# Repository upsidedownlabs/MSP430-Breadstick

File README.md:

# MSP430 Breadstick

Upside Down Labs MSP430 Breadstick is a development board for ultra low power MSP430G2553 MCU from Texas Instruments. 

## Variant: Cheese Dip
Cheese Dip variant of MSP430 Breadstick comes with CH340C USB to UART bridge.

| Front              |  Back |
| :-------------------------: | :-------------------------: |
|   |  |

|Pinout|
| :--: |
||

| Dimensions              |  Schematic |
| :-------------------------: | :-------------------------: |
| 60.00 x 21.60 mm  |  |

## Variant: Apple Sauce
Apple Sauce variant of MSP430 Breadstick comes with FT232RQ USB to UART bridge.

| Front              |  Back |
| :-------------------------: | :-------------------------: |
|   |  |

| Dimensions              |  Schematic |
| :-------------------------: | :-------------------------: |
| 65.786 x 18.542 mm  |  |

## License

#### Hardware
CERN Open Hardware License Version 2 - Strongly Reciprocal ([CERN-OHL-S-2.0](https://spdx.org/licenses/CERN-OHL-S-2.0.html)).

#### Software
MIT open source [license](http://opensource.org/licenses/MIT).

#### Documentation:
<br />This work is licensed under a <a rel="license" href="http://creativecommons.org/licenses/by/4.0/">Creative Commons Attribution 4.0 International License</a>.

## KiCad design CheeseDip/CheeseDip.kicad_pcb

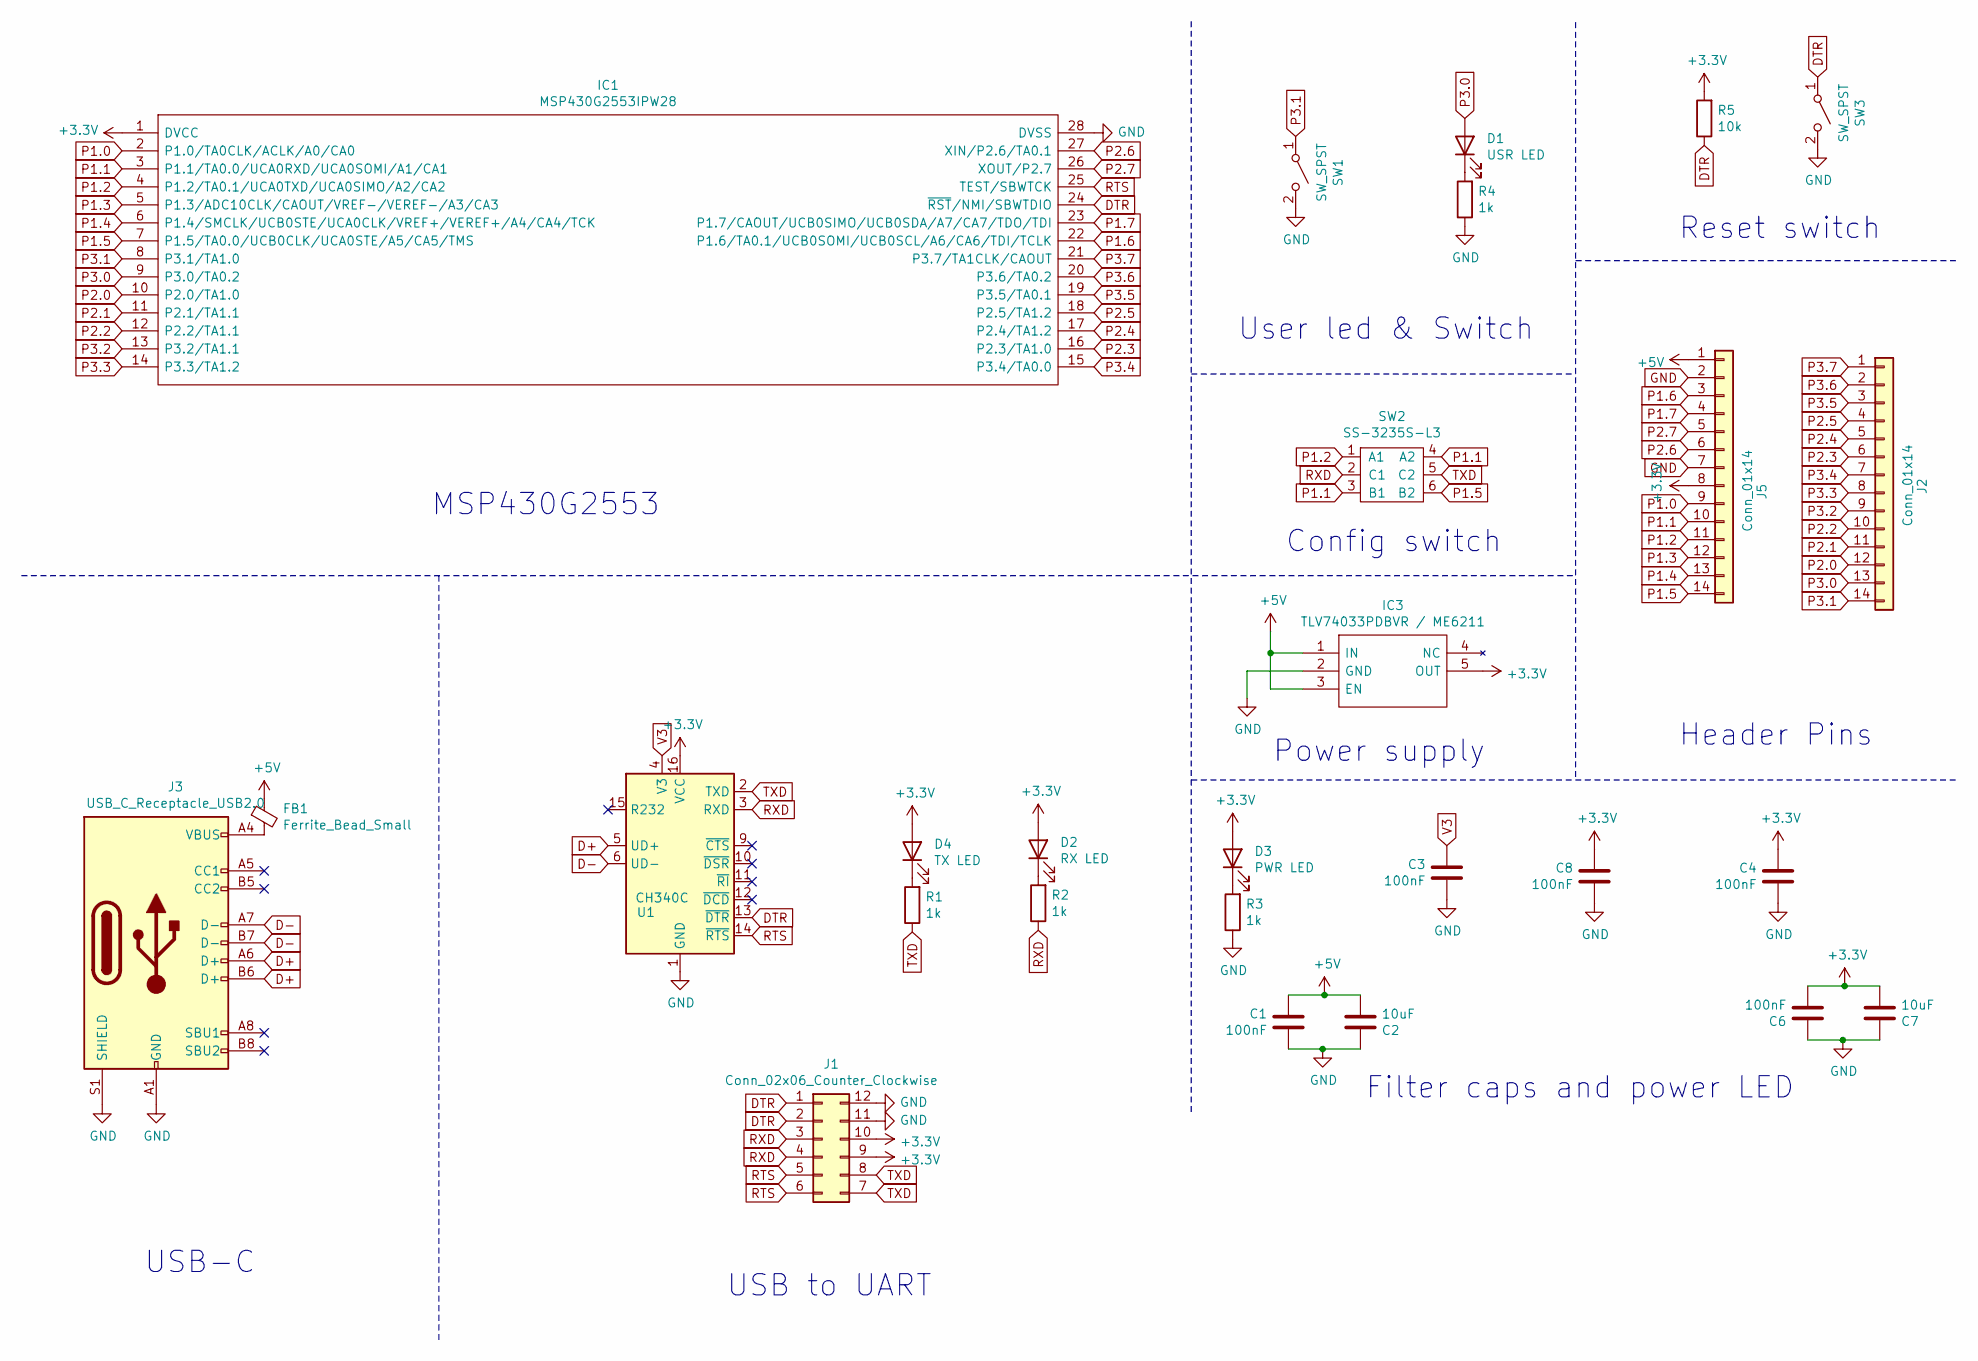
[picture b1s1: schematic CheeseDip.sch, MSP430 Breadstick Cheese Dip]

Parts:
C1, C3, C4, C6, C8: 100nF; C_0603_1608Metric_Pad1.08x0.95mm_HandSolder
C2, C7: 10uF; C_0805_2012Metric_Pad1.18x1.45mm_HandSolder
D1: USR LED; LED_0603_1608Metric_Pad1.05x0.95mm_HandSolder
D2: RX LED; LED_0603_1608Metric_Pad1.05x0.95mm_HandSolder
D3: PWR LED; LED_0603_1608Metric_Pad1.05x0.95mm_HandSolder
D4: TX LED; LED_0603_1608Metric_Pad1.05x0.95mm_HandSolder
FB1: Ferrite_Bead_Small; L_0805_2012Metric_Pad1.15x1.40mm_HandSolder
IC1: MSP430G2553IPW28; Manufacturer_Part_Number MSP430G2553IPW28; Mouser Part Number 595-MSP430G2553IPW28
IC3: TLV74033PDBVR / ME6211; TLV74033PDBVR; Manufacturer_Part_Number TLV74033PDBVR
J1: Conn_02x06_Counter_Clockwise; progMSP
J2, J5: Conn_01x14; PinHeader_1x14_P2.54mm_Vertical
J3: USB_C_Receptacle_USB2.0; USB_C_Receptacle_HRO_TYPE-C-31-M-12
R1, R2, R3, R4: 1k; R_0603_1608Metric_Pad0.98x0.95mm_HandSolder
R5: 10k; R_0603_1608Metric_Pad0.98x0.95mm_HandSolder
SW1, SW3: SW_SPST; SW_SPST_SKQG_WithStem
SW2: SS-3235S-L3
U1: CH340C; SOIC-16_3.9x9.9mm_P1.27mm

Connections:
+3V3: C4.1, C6.2, C7.2, C8.1, D2.2 (A), D3.2 (A), D4.2 (A), IC1.1 (DVCC), IC3.5 (OUT), J1.9, J1.10, J5.8, R5.2, U1.16 (VCC)
+5V: C1.1, C2.2, FB1.1, IC3.1 (IN), IC3.3 (EN), J5.1
D+: J3.A6 (D+), J3.B6 (D+), U1.5 (UD+)
D-: J3.A7 (D-), J3.B7 (D-), U1.6 (UD-)
DTR: IC1.24 (~RST~/NMI/SBWTDIO), J1.1, J1.2, R5.1, SW3.1 (A), U1.13 (~DTR)
GND: C1.2, C2.1, C3.2, C4.2, C6.1, C7.1, C8.2, IC1.28 (DVSS), IC3.2 (GND), J1.11, J1.12, J3.A1 (GND), J3.A12 (GND), J3.B1 (GND), J3.B12 (GND), J3.S1 (SHIELD), J5.2, J5.7, R3.1, R4.1, SW1.2 (B), SW3.2 (B), U1.1 (GND)
unnamed: D1.1 (K), R4.2
unnamed: D2.1 (K), R2.2
unnamed: D3.1 (K), R3.2
unnamed: D4.1 (K), R1.2
unnamed: FB1.2, J3.A4 (VBUS), J3.A9 (VBUS), J3.B4 (VBUS), J3.B9 (VBUS)
P1.0: IC1.2 (P1.0/TA0CLK/ACLK/A0/CA0), J5.9
P1.1: IC1.3 (P1.1/TA0.0/UCA0RXD/UCA0SOMI/A1/CA1), J5.10, SW2.3 (B1), SW2.4 (A2)
P1.2: IC1.4 (P1.2/TA0.1/UCA0TXD/UCA0SIMO/A2/CA2), J5.11, SW2.1 (A1)
P1.3: IC1.5 (P1.3/ADC10CLK/CAOUT/VREF-/VEREF-/A3/CA3), J5.12
P1.4: IC1.6 (P1.4/SMCLK/UCB0STE/UCA0CLK/VREF+/VEREF+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), J5.13
P1.5: IC1.7 (P1.5/TA0.0/UCB0CLK/UCA0STE/A5/CA5/TMS), J5.14, SW2.6 (B2)
P1.6: IC1.22 (P1.6/TA0.1/UCB0SOMI/UCB0SCL/A6/CA6/TDI/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), J5.3
P1.7: IC1.23 (P1.7/CAOUT/UCB0SIMO/UCB0SDA/A7/CA7/TDO/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), J5.4
P2.0: IC1.10 (P2.0/TA1.0), J2.12
P2.1: IC1.11 (P2.1/TA1.1), J2.11
P2.2: IC1.12 (P2.2/TA1.1), J2.10
P2.3: IC1.16 (P2.3/TA1.0), J2.6
P2.4: IC1.17 (P2.4/TA1.2), J2.5
P2.5: IC1.18 (P2.5/TA1.2), J2.4
P2.6: IC1.27 (XIN/P2.6/TA0.1), J5.6
P2.7: IC1.26 (XOUT/P2.7), J5.5
P3.0: D1.2 (A), IC1.9 (P3.0/TA0.2), J2.13
P3.1: IC1.8 (P3.1/TA1.0), J2.14, SW1.1 (A)
P3.2: IC1.13 (P3.2/TA1.1), J2.9
P3.3: IC1.14 (P3.3/TA1.2), J2.8
P3.4: IC1.15 (P3.4/TA0.0), J2.7
P3.5: IC1.19 (P3.5/TA0.1), J2.3
P3.6: IC1.20 (P3.6/TA0.2), J2.2
P3.7: IC1.21 (P3.7/TA1CLK/CAOUT), J2.1
RTS: IC1.25 (TEST/SBWTCK), J1.5, J1.6, U1.14 (~RTS)
RXD: J1.3, J1.4, R2.1, SW2.2 (C1), U1.3 (RXD)
TXD: J1.7, J1.8, R1.1, SW2.5 (C2), U1.2 (TXD)
V3: C3.1, U1.4 (V3)

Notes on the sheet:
MSP430G2553
USB to UART
USB-C
Power supply
Header Pins
Config switch
User led & Switch
Reset switch
Filter caps and power LED

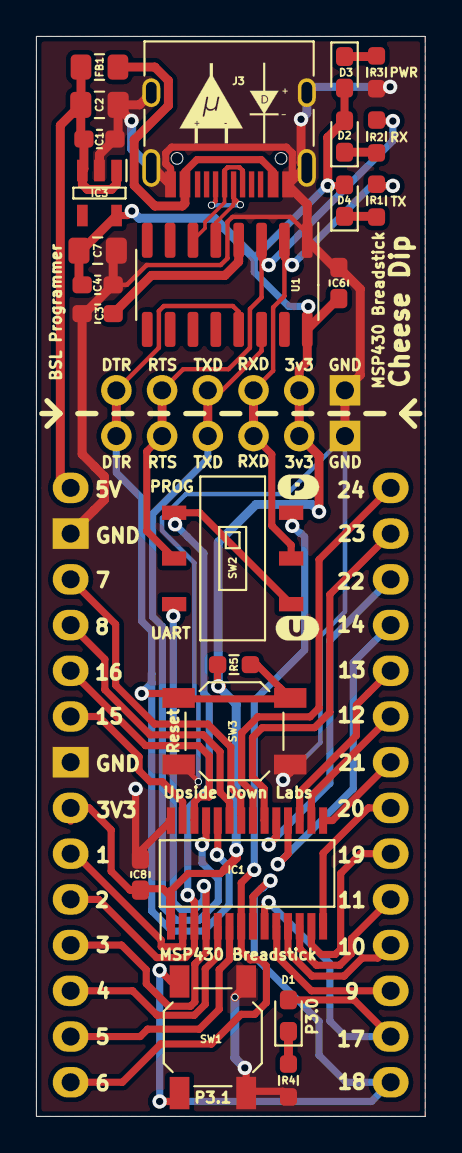
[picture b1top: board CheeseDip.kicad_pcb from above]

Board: 2 copper layers, 21.6 x 60.0 mm, 27 parts (0 on the bottom side), 39 nets.

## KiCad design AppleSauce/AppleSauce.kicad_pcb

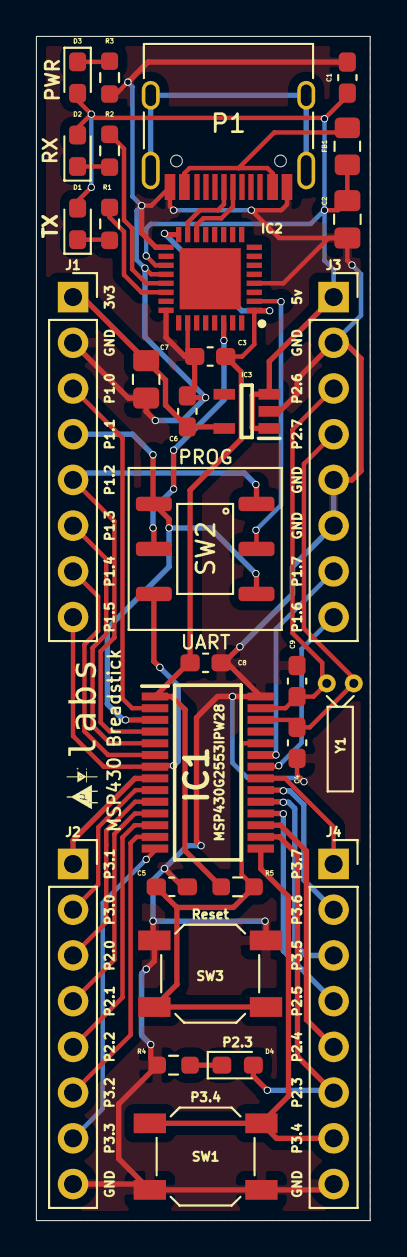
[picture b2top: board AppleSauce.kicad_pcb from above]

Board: 2 copper layers, 18.5 x 65.8 mm, 31 parts (0 on the bottom side), 40 nets.

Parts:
C1, C3, C5, C6, C8: 100nF; C_0603_1608Metric_Pad1.08x0.95mm_HandSolder
C2, C7: 10uF; C_0805_2012Metric_Pad1.18x1.45mm_HandSolder
C4, C9: 22pF; C_0603_1608Metric_Pad1.08x0.95mm_HandSolder
D1: TX LED; LED_0603_1608Metric_Pad1.05x0.95mm_HandSolder
D2: RX LED; LED_0603_1608Metric_Pad1.05x0.95mm_HandSolder
D3: PWR LED; LED_0603_1608Metric_Pad1.05x0.95mm_HandSolder
D4: USR LED; LED_0603_1608Metric_Pad1.05x0.95mm_HandSolder
FB1: Ferrite_Bead_Small; L_0805_2012Metric_Pad1.15x1.40mm_HandSolder
IC1: MSP430G2553IPW28
IC2: FT232RQ
IC3: TLV74033PDBVR
J1, J2, J3, J4: Conn_01x08_Male; PinSocket_1x08_P2.54mm_Vertical
P1: USB_C_Plug_USB2.0; USB_C_Receptacle_HRO_TYPE-C-31-M-12
R1, R2, R3, R4: 1k; R_0603_1608Metric_Pad0.98x0.95mm_HandSolder
R5: 10k; R_0603_1608Metric_Pad0.98x0.95mm_HandSolder
SW1, SW3: SW_SPST; SW_SPST_SKQG_WithStem
SW2: MSS22D18
Y1: 32768 Hz; Crystal_DS10_D1.0mm_L4.3mm_Horizontal

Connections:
3.3v: C3.2, C8.2, IC1.1, IC2.1, IC2.16, R5.2
3.3v_out: C6.2, C7.2, IC3.5, J1.1
5V: C1.1, C2.2, D1.2, D2.2, D3.2, FB1.1, IC2.19, IC3.1, IC3.3, J3.1
D+: IC2.14, P1.A6
D-: IC2.15, P1.A7
GND: C1.2, C2.1, C3.1, C4.2, C5.1, C6.1, C7.1, C8.1, C9.2, IC1.28, IC2.4, IC2.17, IC2.20, IC2.24, IC2.26, IC3.2, J1.2, J2.8, J3.2, J3.5, J3.6, J4.8, P1.A1, P1.A12, P1.B1, P1.B12, R3.1, R4.1, SW1.2, SW3.2
unnamed: D1.1, R1.2
unnamed: D2.1, R2.2
unnamed: D3.1, R3.2
unnamed: D4.1, R4.2
unnamed: FB1.2, P1.A4, P1.A9, P1.B4, P1.B9
P1.0: IC1.2, J1.3
P1.1: IC1.3, J1.4, SW2.3, SW2.4
P1.2: IC1.4, J1.5, SW2.1
P1.3: IC1.5, J1.6
P1.4: IC1.6, J1.7
P1.5: IC1.7, J1.8, SW2.6
P1.6: IC1.22, J3.8
P1.7: IC1.23, J3.7
P2.0: IC1.10, J2.3
P2.1: IC1.11, J2.4
P2.2: IC1.12, J2.5
P2.3: D4.2, IC1.16, J4.6
P2.4: IC1.17, J4.5
P2.5: IC1.18, J4.4
P2.6: C9.1, IC1.27, J3.3, Y1.1
P2.7: C4.1, IC1.26, J3.4, Y1.2
P3.0: IC1.9, J2.2
P3.1: IC1.8, J2.1
P3.2: IC1.13, J2.6
P3.3: IC1.14, J2.7
P3.4: IC1.15, J4.7, SW1.1
P3.5: IC1.19, J4.3
P3.6: IC1.20, J4.2
P3.7: IC1.21, J4.1
RST: C5.2, IC1.24, R5.1, SW3.1
RXD: IC2.2, SW2.2
RXLED: IC2.21, R2.1
TXD: IC2.30, SW2.5
TXLED: IC2.22, R1.1

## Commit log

2020-12-10 update license
2020-12-10 Add apple sauce to breadstick
2020-12-10 add images apple suace images
2020-12-10 add shematic for apple sauce
2020-12-11 update project
    add 3d models and create new silkscreen elements.
2020-12-11 update images
    add schematic and update presious images.
2020-12-11 update readme
    New high-contrast schematic image added.
2021-01-20 Added Breadstick KiCAD-Template.
    - Use these files to create shields. It provides you pre designed board outlines and connector.
2021-01-29 Update Apple Sauce board
2021-01-29 Update Apple Sauce images
2021-01-31 rename
2021-01-31 add Cheese Dip KiCad files
    These KiCAD files are for Cheese Dip variant of MSP430 Breadstick.
2021-01-31 add Cheese Dip images
2021-01-31 add Cheese Dip schematic
2021-02-10 Add colorful CheeseDip images
2021-02-10 Add CheeseDip pinout image
2021-02-10 add 3D
2021-02-10 remove parts csv
2021-02-10 Fix silkscreen
2021-02-10 Update Readme
    Dimensions were swapped, fixed now ;)
2021-02-10 Update pinout diagram
2021-02-18 update pinout
